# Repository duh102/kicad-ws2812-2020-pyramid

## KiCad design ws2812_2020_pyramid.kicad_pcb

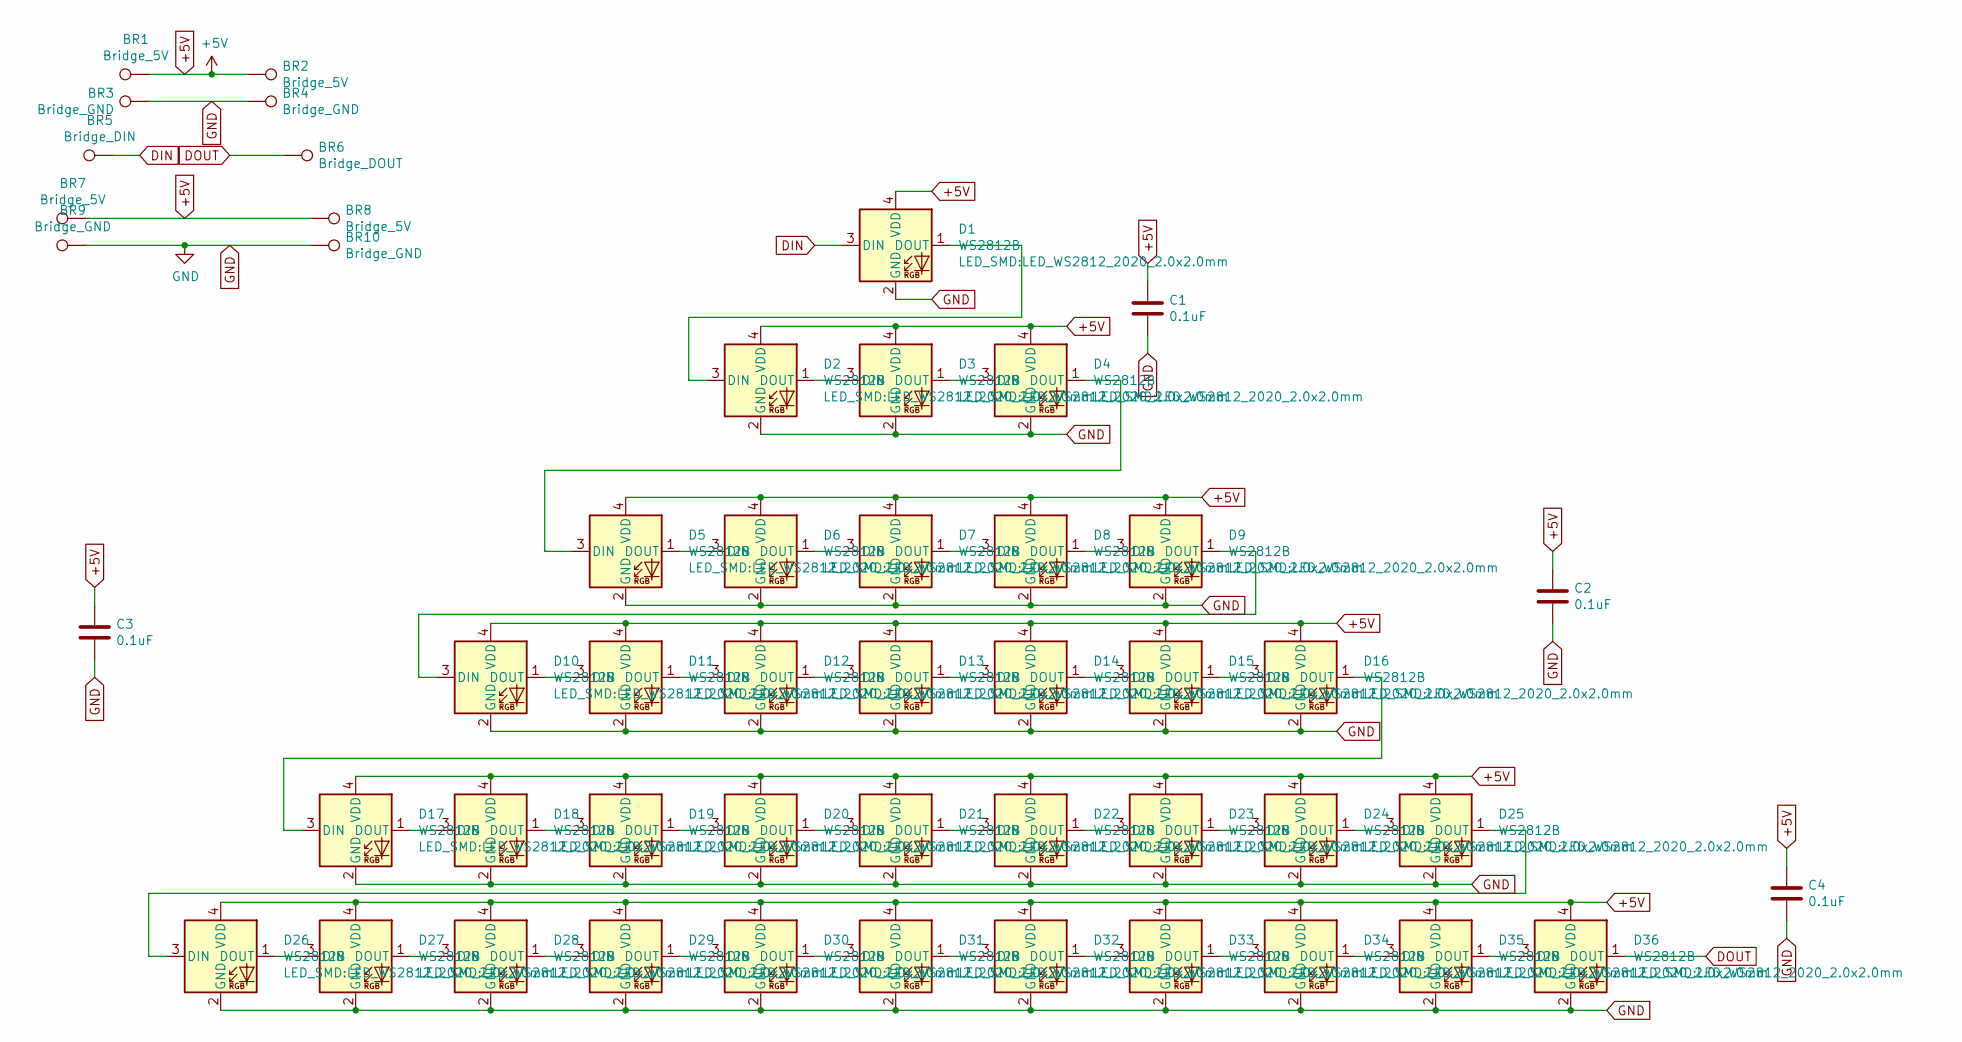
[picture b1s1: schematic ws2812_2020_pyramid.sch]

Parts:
BR1, BR2, BR7, BR8: Bridge_5V; TestPoint_Pad_2.0x2.0mm
BR3, BR4, BR9, BR10: Bridge_GND; TestPoint_Pad_2.0x2.0mm
BR5: Bridge_DIN; TestPoint_Pad_2.0x2.0mm
BR6: Bridge_DOUT; TestPoint_Pad_2.0x2.0mm
C1, C2, C3, C4: 0.1uF; C_0805_2012Metric
D1, D2, D3, D4, D5, D6, D7, D8, D9, D10, D11, D12, D13, D14, D15, D16, D17, D18, D19, D20, D21, D22, D23, D24, D25, D26, D27, D28, D29, D30, D31, D32, D33, D34, D35, D36: WS2812B; LED_WS2812_2020_2.0x2.0mm

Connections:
+5V: BR1.1, BR2.1, BR7.1, BR8.1, C1.1, C2.1, C3.1, C4.1, D1.4 (VDD), D2.4 (VDD), D3.4 (VDD), D4.4 (VDD), D5.4 (VDD), D6.4 (VDD), D7.4 (VDD), D8.4 (VDD), D9.4 (VDD), D10.4 (VDD), D11.4 (VDD), D12.4 (VDD), D13.4 (VDD), D14.4 (VDD), D15.4 (VDD), D16.4 (VDD), D17.4 (VDD), D18.4 (VDD), D19.4 (VDD), D20.4 (VDD), D21.4 (VDD), D22.4 (VDD), D23.4 (VDD), D24.4 (VDD), D25.4 (VDD), D26.4 (VDD), D27.4 (VDD), D28.4 (VDD), D29.4 (VDD), D30.4 (VDD), D31.4 (VDD), D32.4 (VDD), D33.4 (VDD), D34.4 (VDD), D35.4 (VDD), D36.4 (VDD)
DIN: BR5.1, D1.3 (DIN)
DOUT: BR6.1, D36.1 (DOUT)
GND: BR3.1, BR4.1, BR9.1, BR10.1, C1.2, C2.2, C3.2, C4.2, D1.2 (GND), D2.2 (GND), D3.2 (GND), D4.2 (GND), D5.2 (GND), D6.2 (GND), D7.2 (GND), D8.2 (GND), D9.2 (GND), D10.2 (GND), D11.2 (GND), D12.2 (GND), D13.2 (GND), D14.2 (GND), D15.2 (GND), D16.2 (GND), D17.2 (GND), D18.2 (GND), D19.2 (GND), D20.2 (GND), D21.2 (GND), D22.2 (GND), D23.2 (GND), D24.2 (GND), D25.2 (GND), D26.2 (GND), D27.2 (GND), D28.2 (GND), D29.2 (GND), D30.2 (GND), D31.2 (GND), D32.2 (GND), D33.2 (GND), D34.2 (GND), D35.2 (GND), D36.2 (GND)
unnamed: D1.1 (DOUT), D2.3 (DIN)
unnamed: D2.1 (DOUT), D3.3 (DIN)
unnamed: D3.1 (DOUT), D4.3 (DIN)
unnamed: D4.1 (DOUT), D5.3 (DIN)
unnamed: D5.1 (DOUT), D6.3 (DIN)
unnamed: D6.1 (DOUT), D7.3 (DIN)
unnamed: D7.1 (DOUT), D8.3 (DIN)
unnamed: D8.1 (DOUT), D9.3 (DIN)
unnamed: D10.1 (DOUT), D11.3 (DIN)
unnamed: D9.1 (DOUT), D10.3 (DIN)
unnamed: D11.1 (DOUT), D12.3 (DIN)
unnamed: D12.1 (DOUT), D13.3 (DIN)
unnamed: D13.1 (DOUT), D14.3 (DIN)
unnamed: D14.1 (DOUT), D15.3 (DIN)
unnamed: D15.1 (DOUT), D16.3 (DIN)
unnamed: D16.1 (DOUT), D17.3 (DIN)
unnamed: D17.1 (DOUT), D18.3 (DIN)
unnamed: D18.1 (DOUT), D19.3 (DIN)
unnamed: D19.1 (DOUT), D20.3 (DIN)
unnamed: D20.1 (DOUT), D21.3 (DIN)
unnamed: D21.1 (DOUT), D22.3 (DIN)
unnamed: D22.1 (DOUT), D23.3 (DIN)
unnamed: D23.1 (DOUT), D24.3 (DIN)
unnamed: D24.1 (DOUT), D25.3 (DIN)
unnamed: D25.1 (DOUT), D26.3 (DIN)
unnamed: D26.1 (DOUT), D27.3 (DIN)
unnamed: D27.1 (DOUT), D28.3 (DIN)
unnamed: D28.1 (DOUT), D29.3 (DIN)
unnamed: D29.1 (DOUT), D30.3 (DIN)
unnamed: D30.1 (DOUT), D31.3 (DIN)
unnamed: D31.1 (DOUT), D32.3 (DIN)
unnamed: D32.1 (DOUT), D33.3 (DIN)
unnamed: D33.1 (DOUT), D34.3 (DIN)
unnamed: D34.1 (DOUT), D35.3 (DIN)
unnamed: D35.1 (DOUT), D36.3 (DIN)

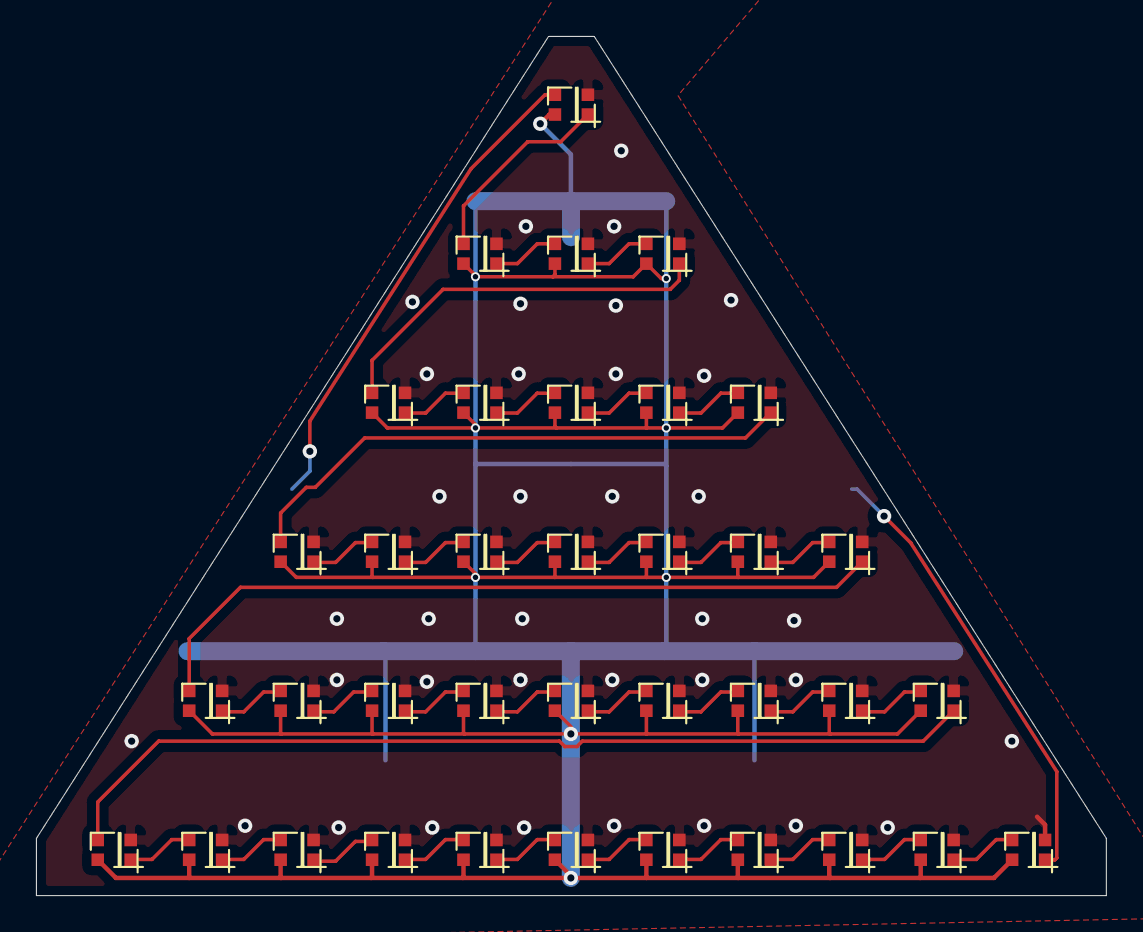
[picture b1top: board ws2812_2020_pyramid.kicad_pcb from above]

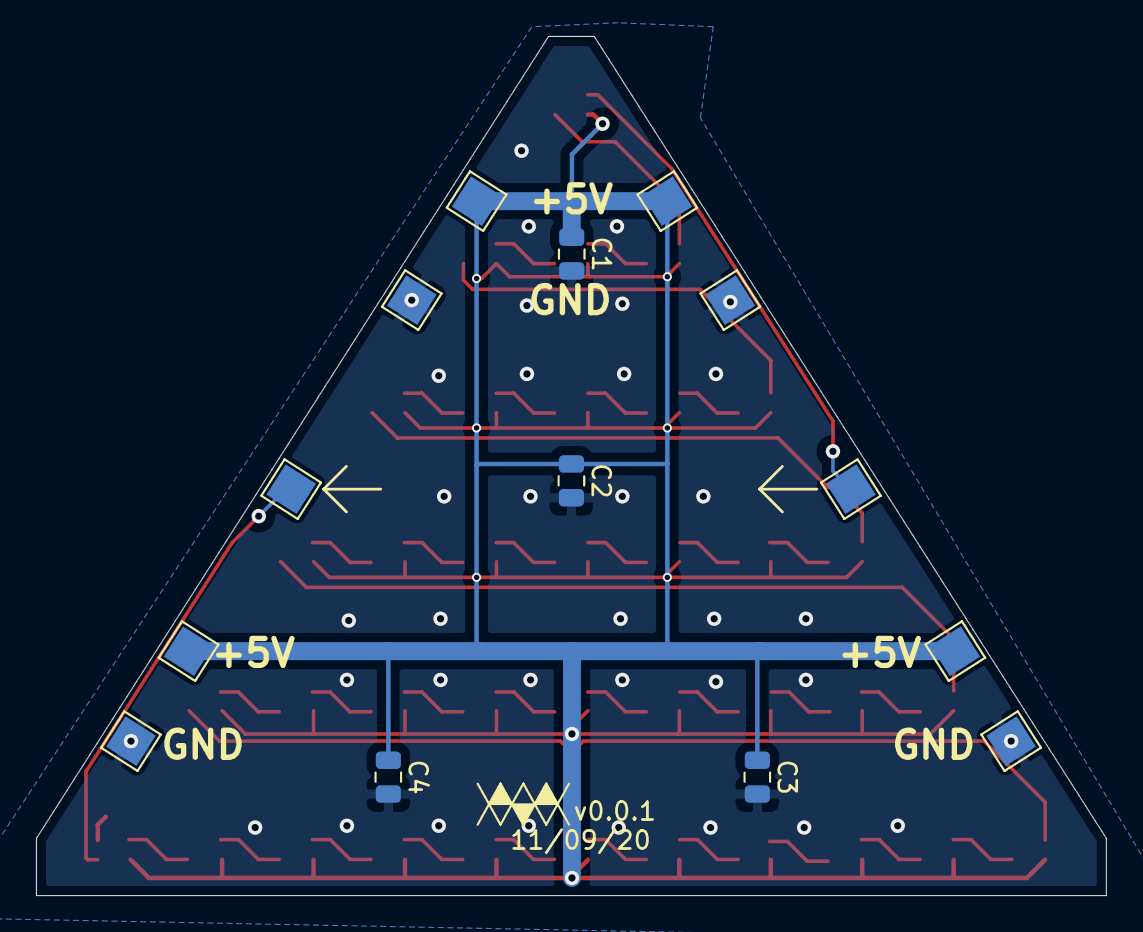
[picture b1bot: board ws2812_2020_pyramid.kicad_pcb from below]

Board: 2 copper layers, 59.4 x 47.7 mm, 50 parts (14 on the bottom side), 39 nets.

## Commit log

2020-10-30 Initial commit, v0.0.0
2020-12-09 Finish design
